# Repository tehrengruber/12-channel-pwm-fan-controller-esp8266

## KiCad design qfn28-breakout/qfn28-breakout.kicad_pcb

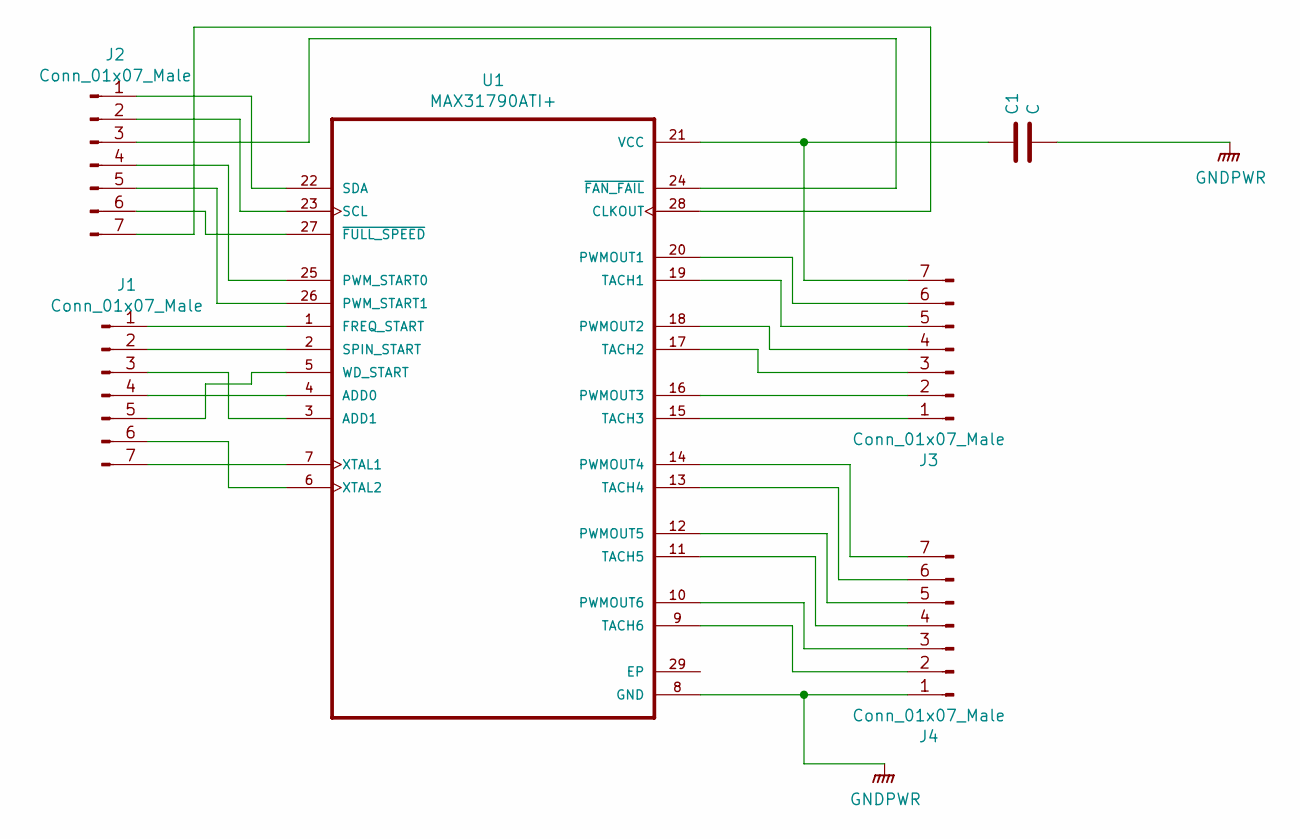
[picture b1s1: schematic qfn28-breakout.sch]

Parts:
C1: C; C_0805_2012Metric
J1, J2, J3, J4: Conn_01x07_Male; PinSocket_1x07_P2.54mm_Vertical
U1: MAX31790ATI+; QFN-28-1EP_4x4mm_P0.4mm_EP2.3x2.3mm_ThermalVias

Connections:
GNDPWR: C1.2, J4.1, U1.8 (GND), U1.29 (EP)
unnamed: C1.1, J3.7, U1.21 (VCC)
unnamed: J1.1, U1.1 (FREQ_START)
unnamed: J1.2, U1.2 (SPIN_START)
unnamed: J1.3, U1.3 (ADD1)
unnamed: J1.4, U1.4 (ADD0)
unnamed: J1.5, U1.5 (WD_START)
unnamed: J1.6, U1.6 (XTAL2)
unnamed: J1.7, U1.7 (XTAL1)
unnamed: J2.1, U1.22 (SDA)
unnamed: J2.2, U1.23 (SCL)
unnamed: J2.3, U1.24 (~FAN_FAIL~)
unnamed: J2.4, U1.25 (PWM_START0)
unnamed: J2.5, U1.26 (PWM_START1)
unnamed: J2.6, U1.27 (~FULL_SPEED~)
unnamed: J2.7, U1.28 (CLKOUT)
unnamed: J3.1, U1.15 (TACH3)
unnamed: J3.2, U1.16 (PWMOUT3)
unnamed: J3.3, U1.17 (TACH2)
unnamed: J3.4, U1.18 (PWMOUT2)
unnamed: J3.5, U1.19 (TACH1)
unnamed: J3.6, U1.20 (PWMOUT1)
unnamed: J4.2, U1.9 (TACH6)
unnamed: J4.3, U1.10 (PWMOUT6)
unnamed: J4.4, U1.11 (TACH5)
unnamed: J4.5, U1.12 (PWMOUT5)
unnamed: J4.6, U1.13 (TACH4)
unnamed: J4.7, U1.14 (PWMOUT4)

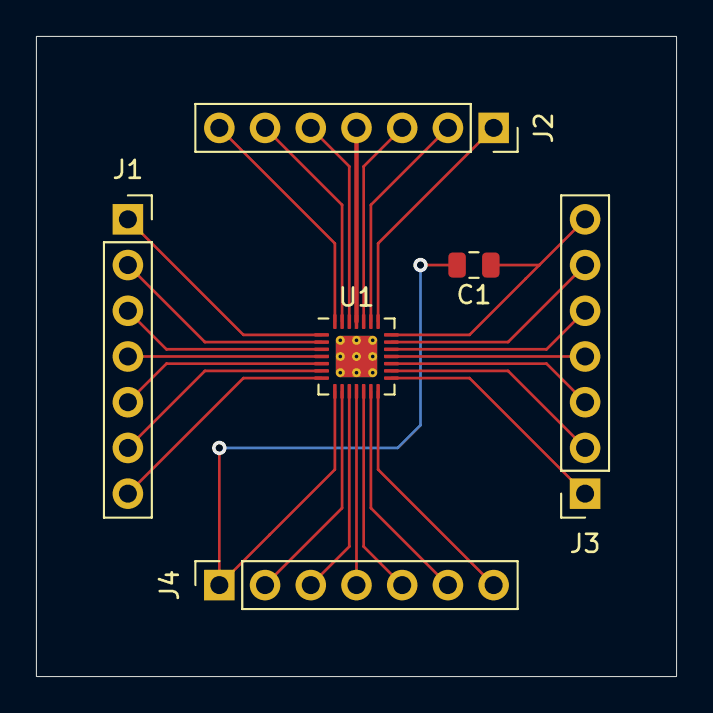
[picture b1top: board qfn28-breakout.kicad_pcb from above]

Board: 2 copper layers, 35.6 x 35.6 mm, 6 parts (0 on the bottom side), 28 nets.

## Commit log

2020-06-03 Added PCB design for qfn28 breakout board (dimensions in the main layout are still wrong)
2020-06-03 Moved decoupling capacitor on qfn28 breakout board
